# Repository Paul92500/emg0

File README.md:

# emg0
Capteur emg (bioamplifier) en open source.
électrodes actives + ampli d'instrumentation
+ arduino + bluetooth
+ réception sur smartphone android

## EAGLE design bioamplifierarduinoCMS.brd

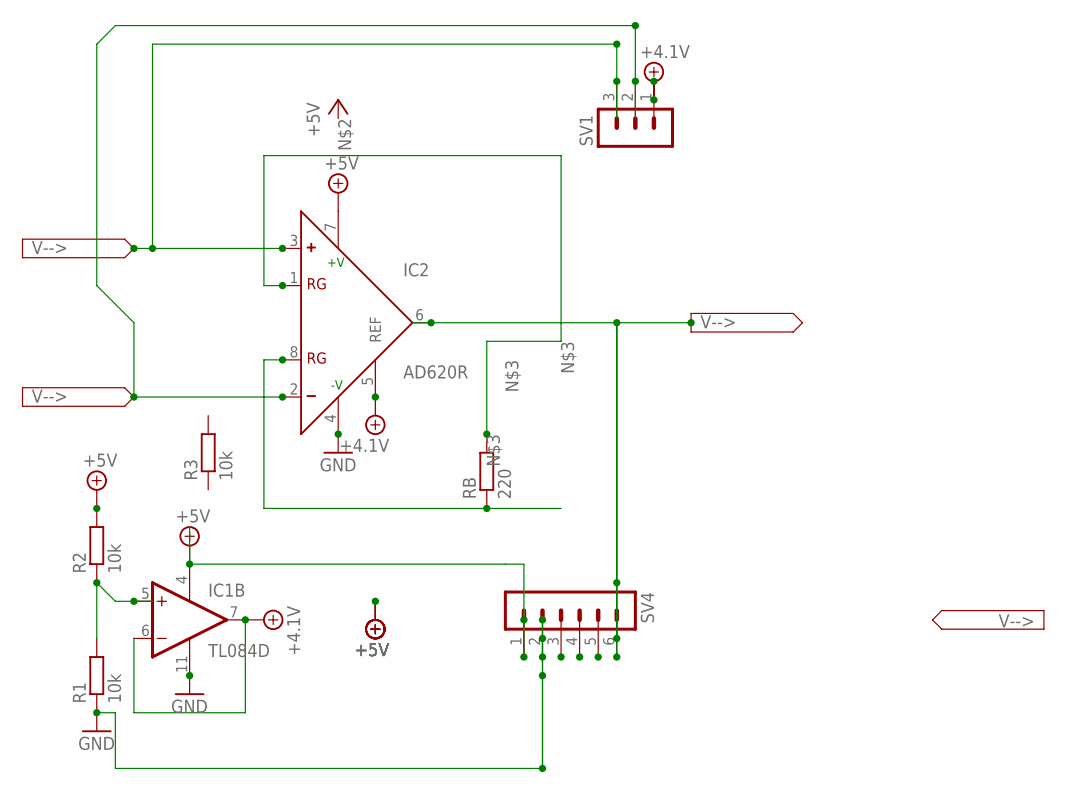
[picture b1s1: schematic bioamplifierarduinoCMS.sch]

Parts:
IC1: TL084D; SO14
IC2: AD620R; SO8; MPN AD620AR
R1, R2, R3: 10k; R1206
RB: 220; R1206
SV1: MA03-1
SV4: MA06-1

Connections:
+4.1V: IC1.6 (-IN), IC1.7 (OUT), IC2.5 (REF)
+5V: IC1.4 (V+), R2.2, SV4.1
GND: IC1.11 (V-), IC2.4 (-V), R1.1, SV4.2
unnamed: IC2.3 (+), SV1.3
unnamed: IC2.1 (RG), RB.2
unnamed: IC1.5 (+IN), R1.2, R2.1
unnamed: IC2.6 (OUT), SV4.6
unnamed: IC2.2 (-), SV1.2
unnamed: IC2.8 (RG), RB.1

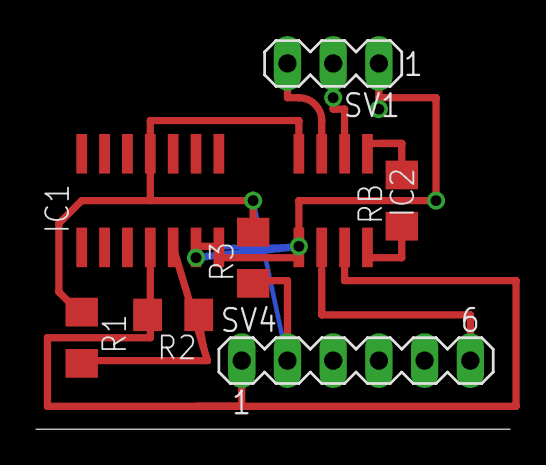
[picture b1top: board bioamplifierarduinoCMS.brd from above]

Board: 2 copper layers, 8 parts (0 on the bottom side), 9 nets.

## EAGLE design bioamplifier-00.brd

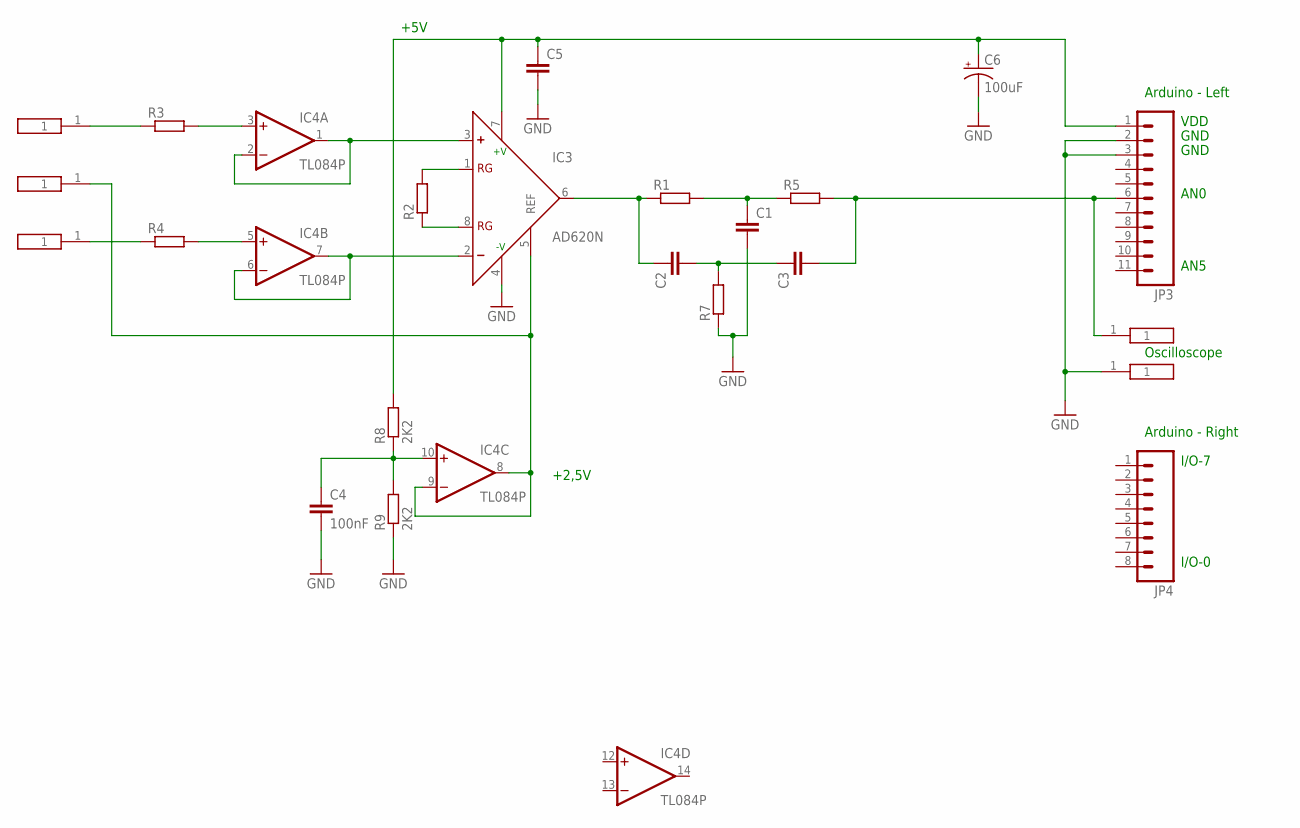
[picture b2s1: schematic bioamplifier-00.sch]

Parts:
C1, C2, C3, C5: C5/3; C5B3
C4: 100nF; C5B3
C6: 100uF; EIA7343
GND: PAD1
IC3: AD620N; DIL08
IC4: TL084P; DIL14
IN1, IN2: PAD1
JP3: M11LONGPADS; 1X11_LONGPADS
JP4: M08LONGPADS; 1X08_LONGPADS
OUT: PAD1
R1, R2, R3, R4, R5, R7: R-EU_0207/10; 0207/10
R8, R9: 2K2; 0207/10
REF: PAD1

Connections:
GND: C1.2, C4.2, C5.2, C6.C (-), GND.1, IC3.4 (-V), JP3.2, JP3.3, R7.1, R9.1
unnamed: C2.1, IC3.6 (OUT), R1.1
unnamed: C1.1, R1.2, R5.1
unnamed: C2.2, C3.1, R7.2
unnamed: C3.2, JP3.6, OUT.1, R5.2
unnamed: IC3.1 (RG), R2.2
unnamed: IC3.8 (RG), R2.1
unnamed: IC3.3 (+), IC4.1 (OUT), IC4.2 (-IN)
unnamed: IC3.2 (-), IC4.6 (-IN), IC4.7 (OUT)
unnamed: C5.1, C6.A (+), IC3.7 (+V), JP3.1, R8.2
unnamed: C4.1, IC4.10 (+IN), R8.1, R9.2
unnamed: IN1.1, R3.1
unnamed: IC4.3 (+IN), R3.2
unnamed: IN2.1, R4.1
unnamed: IC4.5 (+IN), R4.2
unnamed: IC3.5 (REF), IC4.8 (OUT), IC4.9 (-IN), REF.1
V+: IC4.4 (V+)
V-: IC4.11 (V-)

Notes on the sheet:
Arduino - Left
I/O-0
I/O-7
VDD
GND
AN5
AN0
Arduino - Right
+5V
+2,5V
Oscilloscope

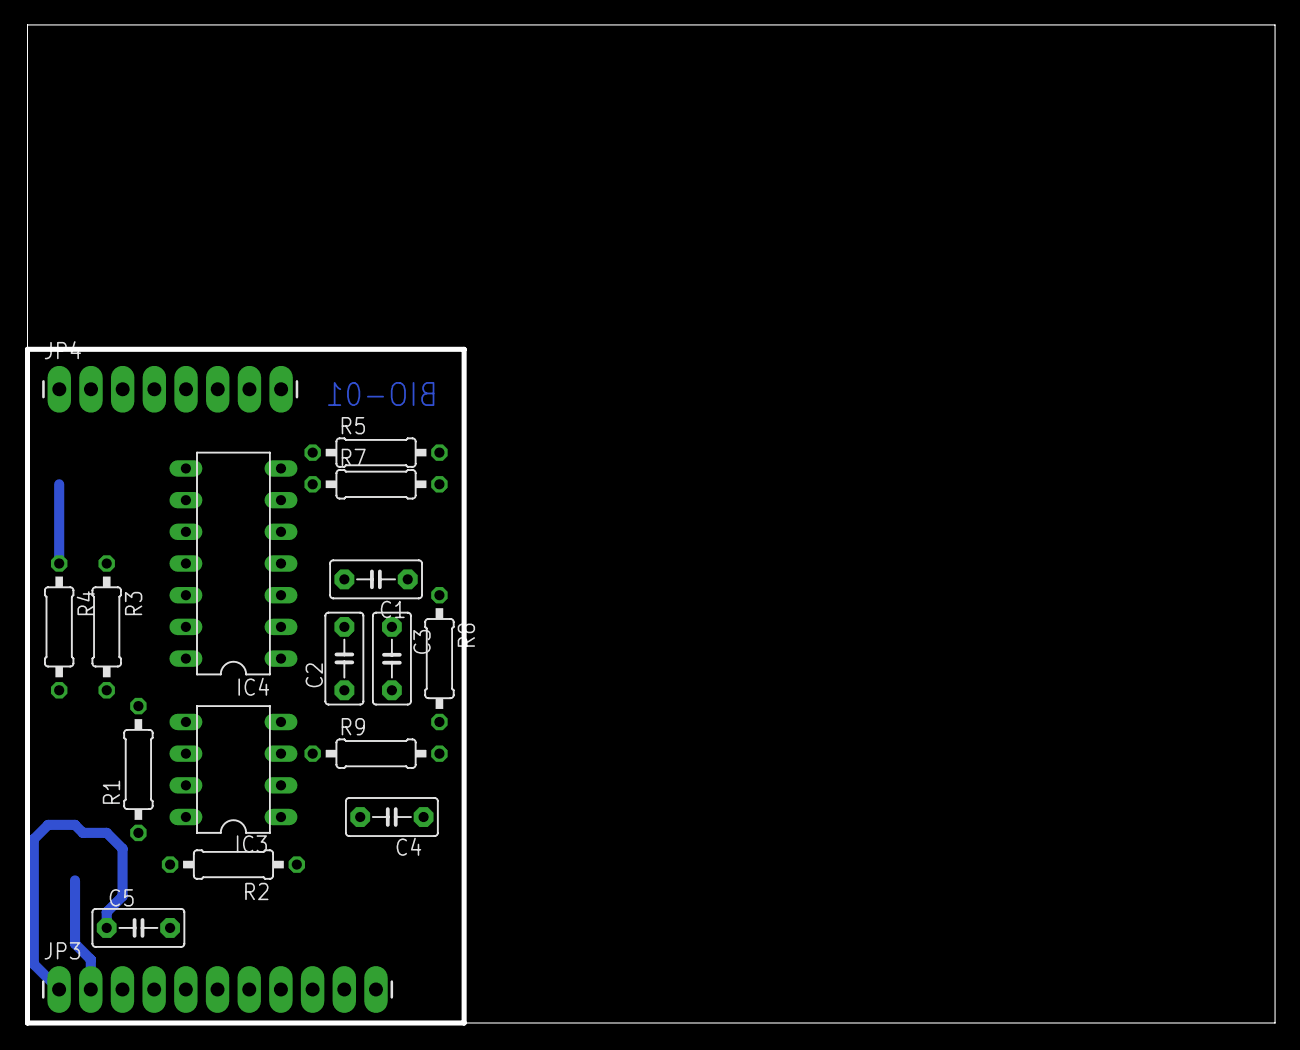
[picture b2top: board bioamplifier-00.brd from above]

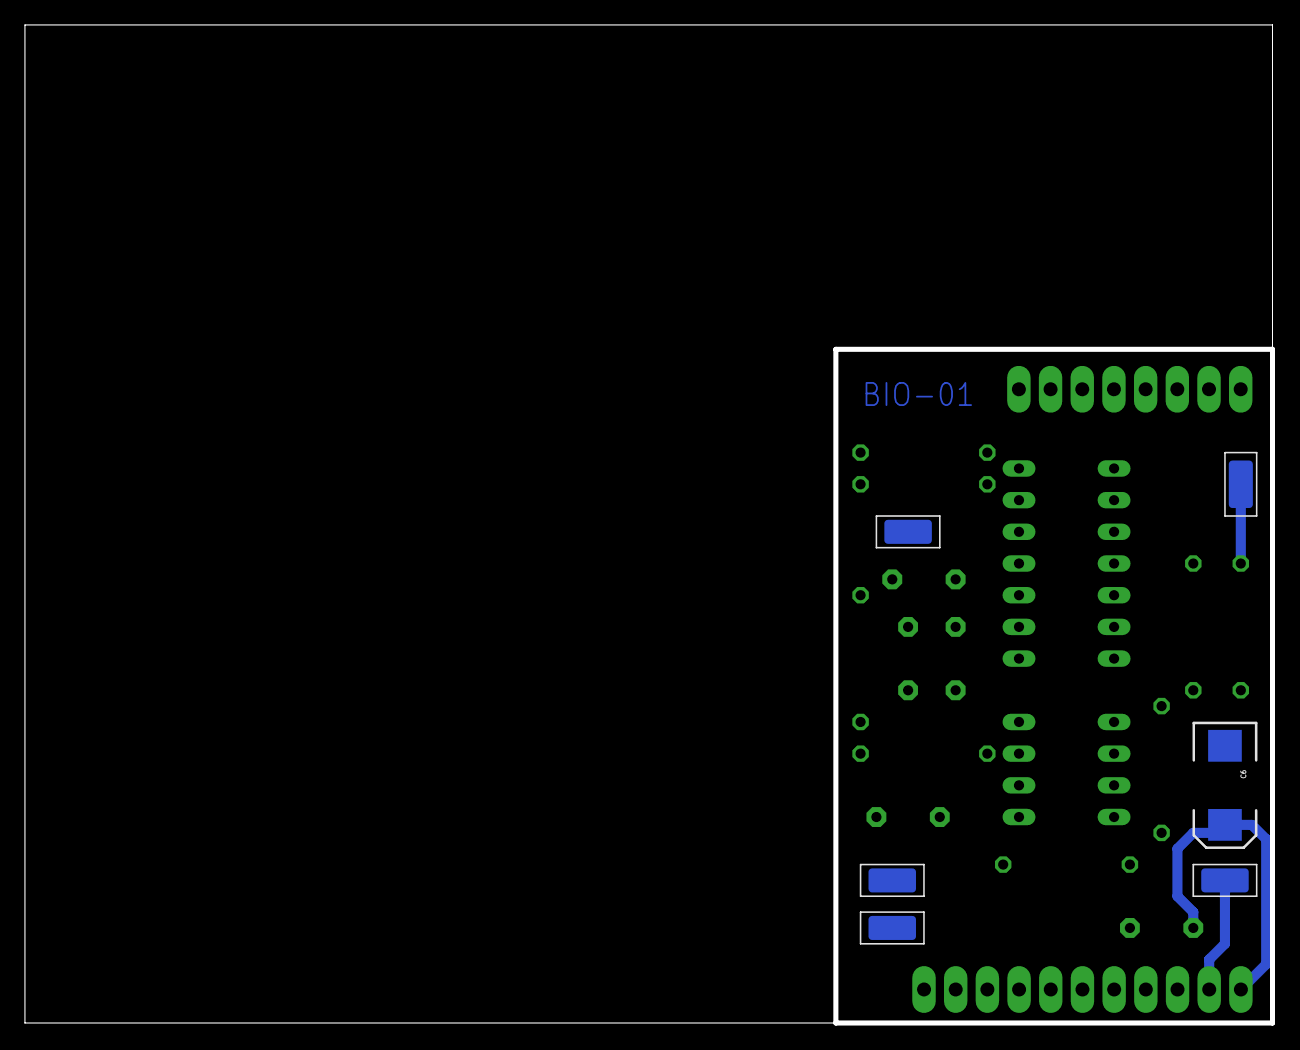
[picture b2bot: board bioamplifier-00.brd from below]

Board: 2 copper layers, 100.0 x 80.0 mm, 23 parts (6 on the bottom side), 16 nets.

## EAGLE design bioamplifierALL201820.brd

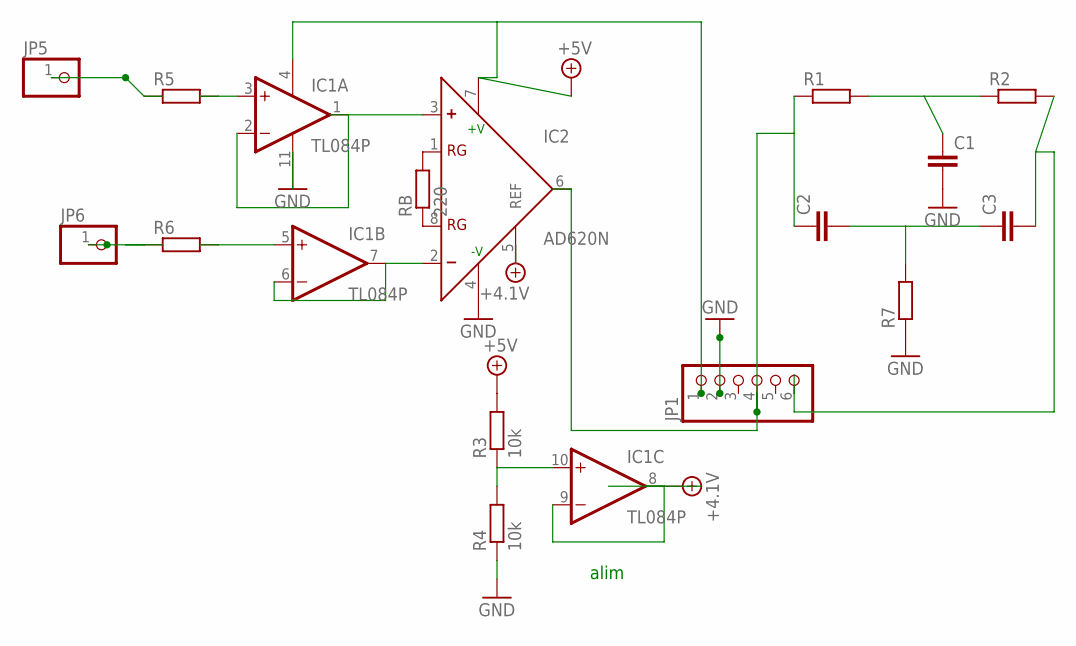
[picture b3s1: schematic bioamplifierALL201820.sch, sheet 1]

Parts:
C1, C2, C3: C-EU050-025X075; C050-025X075
IC1: TL084P; DIL14
IC2: AD620N; DIL08
JP1: PINHD-1X6; 1X06
JP5, JP6: PINHD-1X1; 1X01
R1, R2, R7: R-EU_0204/7; 0204/7
R3, R4: 10k; 0204/5
R5, R6: R-EU_0204/5; 0204/5
RB: 220; 0204/5

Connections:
+4.1V: IC2.5 (REF)
+5V: IC1.4 (V+), IC2.7 (+V), JP1.1, R3.2
GND: C1.2, IC1.11 (V-), IC2.4 (-V), JP1.2, R4.1, R7.1
unnamed: IC1.10 (+IN), R3.1, R4.2
unnamed: IC2.1 (RG), RB.2
unnamed: JP5.1, R5.1
unnamed: IC1.1 (OUT), IC1.2 (-IN), IC2.3 (+)
unnamed: JP6.1, R6.1
unnamed: IC1.5 (+IN), R6.2
unnamed: C1.1, R1.2, R2.1
unnamed: C3.2, JP1.6, R2.2
unnamed: IC2.8 (RG), RB.1
unnamed: IC1.3 (+IN), R5.2
unnamed: C2.1, IC2.6 (OUT), R1.1
unnamed: IC1.8 (OUT), IC1.9 (-IN)
unnamed: C2.2, C3.1, R7.2
unnamed: IC1.6 (-IN), IC1.7 (OUT), IC2.2 (-)

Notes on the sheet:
alim

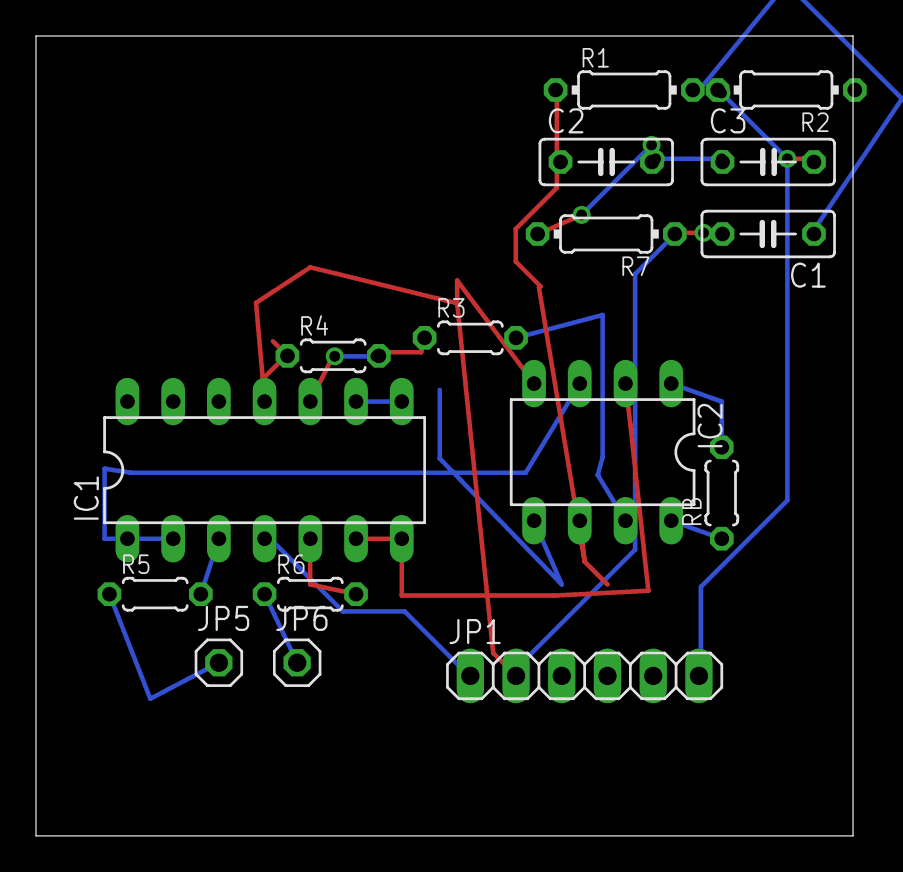
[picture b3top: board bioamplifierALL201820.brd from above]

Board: 2 copper layers, 45.4 x 44.4 mm, 16 parts (0 on the bottom side), 16 nets.

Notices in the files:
parts and their libraries:
SparkFun-Capacitors: Licensing: Creative Commons ShareAlike 4.0 International - https://creativecommons.org/licenses/by-sa/4.0
